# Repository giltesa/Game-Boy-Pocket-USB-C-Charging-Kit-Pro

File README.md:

# Game Boy Pocket USB-C Charging Kit PRO

The **Game Boy Pocket USB-C Charging Kit PRO** is the new circuit for **Nintendo Game Boy Pocket**. This time is all in one circuit and includes not only the **charging controller** but also a **boost converter** and **audio amplifier**.

The modern **IPS displays** with background light require more energy than the stock display. Also, **the flash cards** to load tons of games consume the battery very fast. If you really want to enjoy the games, the best way to do it is using a rechargeable battery instead of AA batteries.

However, that is not enough because a higher consume is forcing the original electronic to strive more than it can. That may cause noise in the speaker or headphones.

Typical solution has been adding a charging circuit for the battery and a power converter to replace the old and not efficiently one which is included in the GBP. Some people also add an audio amplifier to hear better the speaker sound. All these things make the GBP perfect, however the installation require a lot of cables and can not be easy for some people without enough knowledge.

Typical installation of the 3 modules:

*(Thanks Sascha for the photo of his GB **COLOR** installation!)*

For resolving that, this new **Game Boy Pocket USB-C Charging Kit PRO** includes the three circuits in one, everything wired each other, and you will just need to solder a few points to the GBP board.

## FEATURES

-   Exact shape for Game Boy Pocket.
-   Li-Ion battery charger by USB-C with protection for charging level and overdischarge.
-   DC to DC converter (only 5V output, not compatible with the original display).
-   Audio amplifier for the speaker with a potentiometer called VR1 to setup the maximum volume.
-   Integrated LED indicators on the main board, next to the USB for charging battery (red) and full battery (green). It can be disabled by the jumper SJ1.
-   External LED indicators board for playing (white), charging battery (red) and full battery (green). Optional installation.

## Would you like it?

https://shop.giltesa.com/product/game-boy-pocket-usb-c-charging-kit-pro/

## More

- [giltesa.com](https://giltesa.com "giltesa.com")
- [twitter.com](https://twitter.com/giltesa "twitter.com")

## License

This project is licensed under a **Creative Commons** license:
**[Attribution-NonCommercial-ShareAlike 4.0 International (CC BY-NC-SA 4.0) ](https://creativecommons.org/licenses/by-nc-sa/4.0/)**

Check the [LICENSE.md](LICENSE.md) for more information.

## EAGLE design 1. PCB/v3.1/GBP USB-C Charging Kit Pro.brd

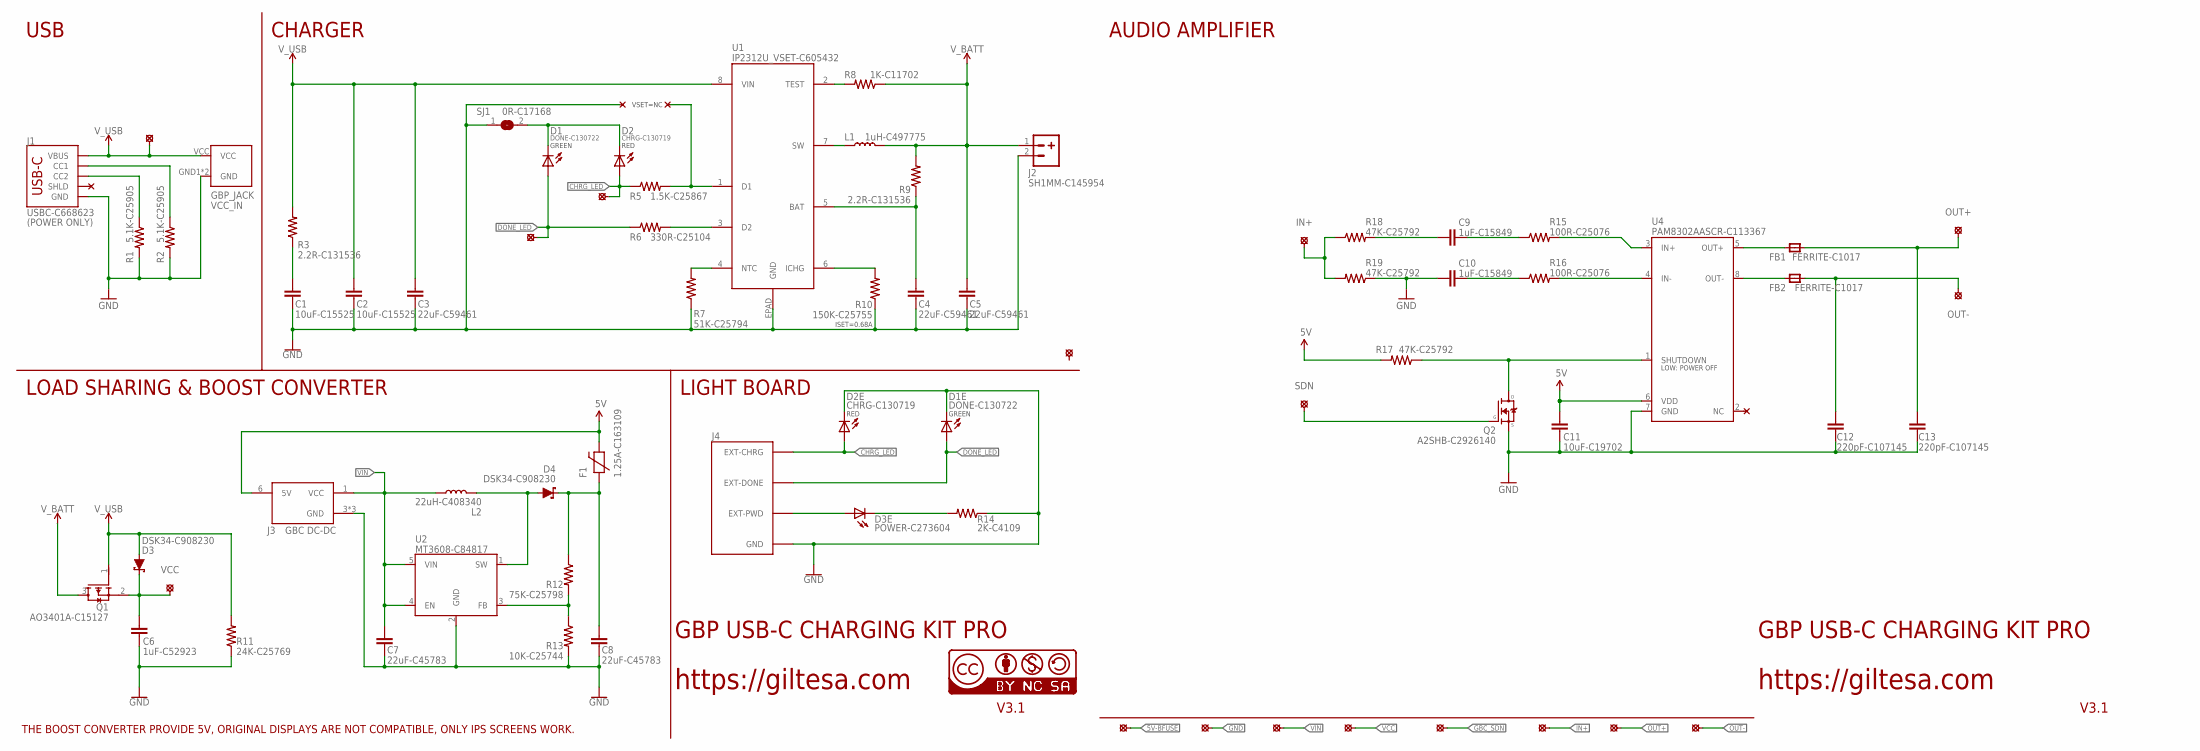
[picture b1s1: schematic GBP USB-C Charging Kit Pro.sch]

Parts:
C1, C2: 10uF-C15525; C0402_S
C3, C4, C5: 22uF-C59461; C0603_S
C6: 1uF-C52923; C0402_S
C7, C8: 22uF-C45783; C0805_S
C9, C10: 1uF-C15849; C0603_S
C11: 10uF-C19702; C0603_S
C12, C13: 220pF-C107145; C0805_S
D1, D1E: DONE-C130722; L0402
D2, D2E: CHRG-C130719; L0402
D3, D4: DSK34-C908230; SOD-123FL
D3E: POWER-C273604; L0402
F1: 1.25A-C163109; F0603_S
FB1, FB2: FERRITE-C1017; MICROBUILDER__0805MP_S
GBP_JACK: VCC_IN; GBP_POWER_JACK_DIP
J1: USBC-C668623; USB-C_6P
J2: SH1MM-C145954; JST-2-1MM-SMD_RIGHT
J3: GBC DC-DC; GBP_DC_DC_DIP_V2
J4: GBP_LED_V2
L1: 1uH-C497775; PSPMAA0402
L2: 22uH-C408340; PSPMAA0402
PP1, PP2, PP3, PP4, PP5, PP6, PP7, PP8: SOLDER_PAD-1.5; SOLDER_PAD_1.5
Q1: AO3401A-C15127; SOT23-3_S
Q2: A2SHB-C2926140; SOT23-3_S
R1, R2: 5.1K-C25905; R0402
R3, R9: 2.2R-C131536; R0402
R5: 1.5K-C25867; R0402
R6: 330R-C25104; R0402
R7: 51K-C25794; R0402
R8: 1K-C11702; R0402
R10: 150K-C25755; R0402
R11: 24K-C25769; R0402
R12: 75K-C25798; R0402
R13: 10K-C25744; R0402
R14: 2K-C4109; R0402
R15, R16: 100R-C25076; R0402
R17, R18, R19: 47K-C25792; R0402
SJ1: 0R-C17168; JUMPER-SMD_0402
U1: IP2312U_VSET-C605432; IP2312
U2: MT3608-C84817; SOT-23-6
U4: PAM8302AASCR-C113367; PAM8302AASCR
U$1: VCC; PAD_1.4
U$2: SDN; PAD_1.25
U$6: CC-BY-NC-SA15MM; CC-BY-NC-SA_15MM
U$20: OUT+; SOLDER_PAD_2.0
U$23: OUT-; SOLDER_PAD_2.0
U$24: CHRG_LED; SOLDER_PAD_1.3
U$25: DONE_LED; SOLDER_PAD_1.3
U$30: IN+; SOLDER_PAD_1.3
U$54: PAD_1.4
U$55: SOLDER_PAD-2.0; SOLDER_PAD_2.0

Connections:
5V: C11.1, F1.2, J3.6 (5V), R17.2, U4.6 (VDD)
5V-BFUSE: C8.2, D4.C, F1.1, PP1.P$1, R12.1
CHRG_LED: D2.A, D2E.A, J4.EXT-CHRG, R5.1, U$24.P$1
DONE_LED: D1.A, D1E.A, J4.EXT-DONE, R6.1, U$25.P$1
GBC_SDN: PP5.P$1, Q2.1 (G), U$2.P$1
GND: C1.1, C2.1, C3.1, C4.1, C5.1, C6.2, C7.1, C8.1, C10.2, C11.2, C12.2, C13.2, D1E.C, D2E.C, GBP_JACK.GND1 (GND), GBP_JACK.GND2 (GND), J1.A12-GND (GND), J1.B12-GND (GND), J2.2, J3.3 (GND), J3.3_1 (GND), J3.3_2 (GND), J4.GND, PP2.P$1, Q2.2 (S), R1.2, R2.2, R7.1, R10.1, R11.1, R13.2, R14.1, R19.1, SJ1.1, U1.EPAD (GND), U2.2 (GND), U4.7 (GND)
IN+: PP6.P$1, R18.1, R19.2, U$30.P$1
unnamed: D1.C, D2.C, SJ1.2
unnamed: D4.A, L2.P$2 (2), U2.1 (SW)
unnamed: J1.B5 (CC2), R1.1
unnamed: R8.2, U1.2 (TEST)
unnamed: R12.2, R13.1, U2.3 (FB)
unnamed: R16.2, U4.4 (IN-)
unnamed: D3E.A, J4.EXT-PWD, J4.EXT-PWD' (EXT-PWD)
unnamed: D3E.C, R14.2
unnamed: R15.2, U4.3 (IN+)
unnamed: J1.A5 (CC1), R2.1
unnamed: C4.2, R9.1, U1.5 (BAT)
unnamed: C1.2, R3.1
unnamed: C10.1, R16.1
unnamed: FB2.1, U4.8 (OUT-)
unnamed: R5.2, U1.1 (D1)
unnamed: FB1.1, U4.5 (OUT+)
unnamed: C9.1, R15.1
unnamed: C9.2, R18.2
unnamed: R7.2, U1.4 (NTC)
unnamed: R10.2, U1.6 (ICHG)
unnamed: R6.2, U1.3 (D2)
unnamed: L1.P$1 (1), U1.7 (SW)
OUT+: C13.1, FB1.2, PP7.P$1, U$20.P$1
OUT-: C12.1, FB2.2, PP8.P$1, U$23.P$1
SDN: Q2.3 (D), R17.1, U4.1 (SHUTDOWN)
VCC: C6.1, D3.C, PP4.P$1, Q1.2 (S), U$1.P$1
VIN: C7.2, J3.1 (VCC), L2.P$1 (1), PP3.P$1, U2.4 (EN), U2.5 (VIN)
V_BATT: C5.2, J2.1, L1.P$2 (2), Q1.3 (D), R8.1, R9.2
V_USB: C2.2, C3.2, D3.A, GBP_JACK.VCC, J1.A9-VBUS (VBUS), J1.B9-VBUS (VBUS), Q1.1 (G), R3.2, R11.2, U1.8 (VIN), U$54.P$1

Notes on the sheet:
GBP USB-C CHARGING KIT PRO
https://giltesa.com
V3.1
(POWER ONLY)
THE BOOST CONVERTER PROVIDE 5V, ORIGINAL DISPLAYS ARE NOT COMPATIBLE, ONLY IPS SCREENS WORK.
USB
CHARGER
LOAD SHARING & BOOST CONVERTER
AUDIO AMPLIFIER
LIGHT BOARD
ISET=0.68A
GREEN
RED
VSET=NC

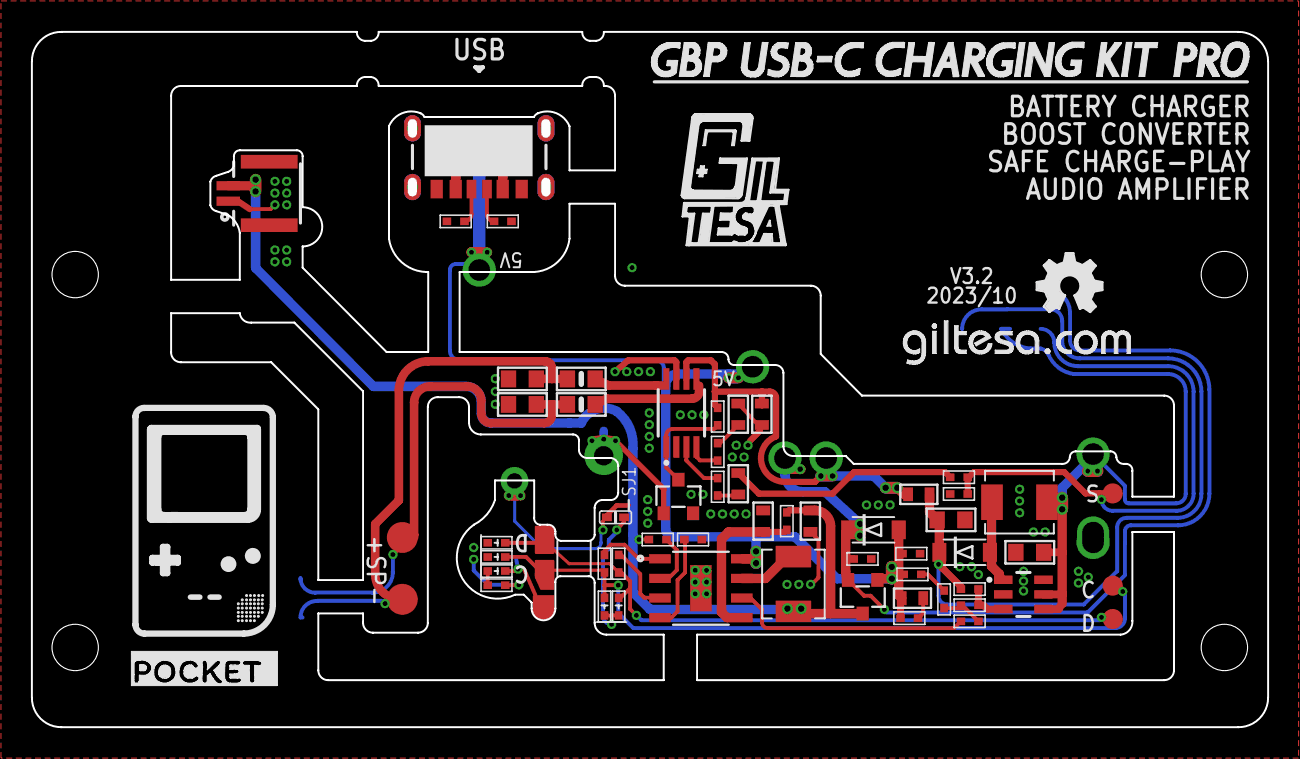
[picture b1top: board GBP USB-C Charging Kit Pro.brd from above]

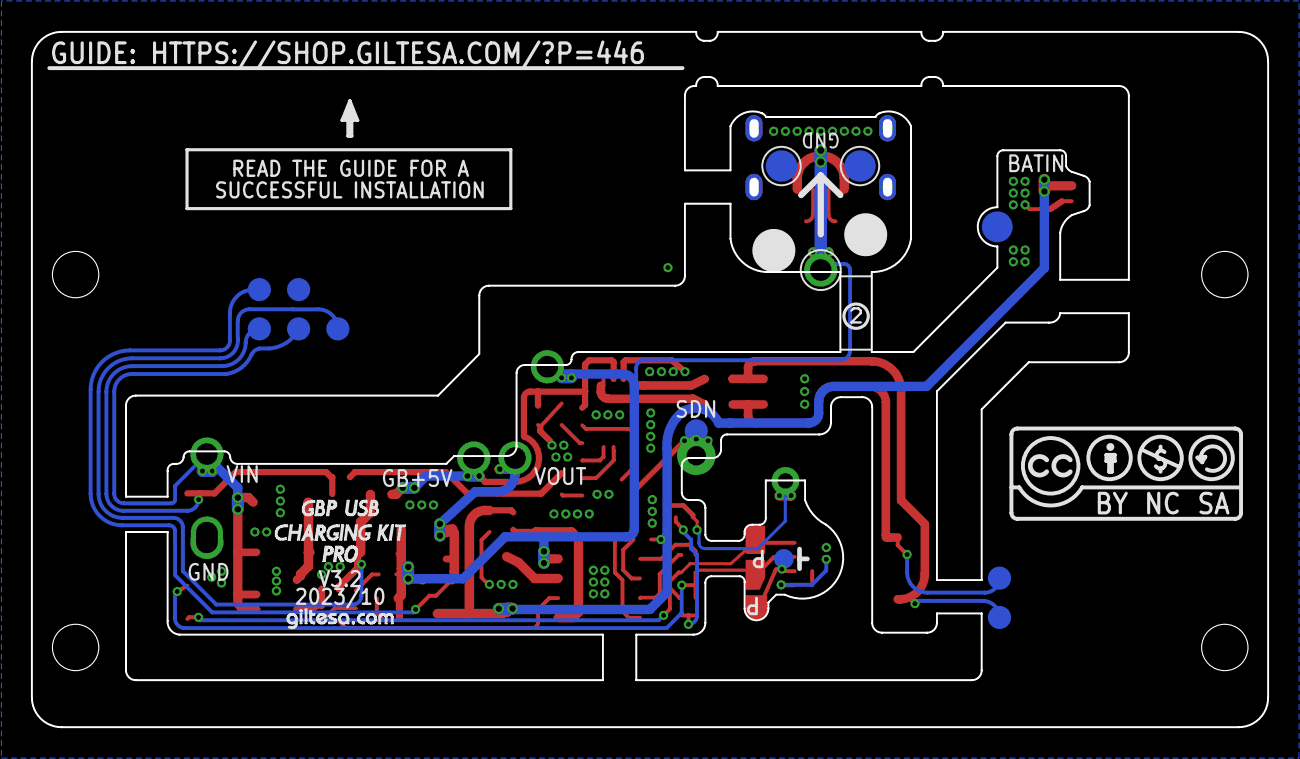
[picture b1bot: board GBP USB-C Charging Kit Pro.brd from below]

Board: 2 copper layers, 79.5 x 44.5 mm, 80 parts (13 on the bottom side), 36 nets.

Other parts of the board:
LOGO1: OSHW_LOGO_FILLX0150-NT; OSHW_FILLX150_NOTEXT
U$3: GILTESA_LOGO_MASK_9MM
U$4: GBP_PRO_FRAME
U$7: GILTESA.COM_MASK
U$31: GBP_FRAME_LOGO
U$34: GAME_BOY_POCKET_USB_CHARGING_KIT_PRO
U$52: GILTESA.COM_MASK_7MM
U$61: SCISSOR_TWO

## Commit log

2023-08-14 no message
2024-01-15 v3.0
2024-01-15 v3.1

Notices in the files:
parts and their libraries:
SparkFun: Licensing: CC v3.0 Share-Alike You are welcome to use this library for commercial purposes.
SparkFun-PowerSymbols: Licensing: Creative Commons ShareAlike 4.0 International - https://creativecommons.org/licenses/by-sa/4.0
